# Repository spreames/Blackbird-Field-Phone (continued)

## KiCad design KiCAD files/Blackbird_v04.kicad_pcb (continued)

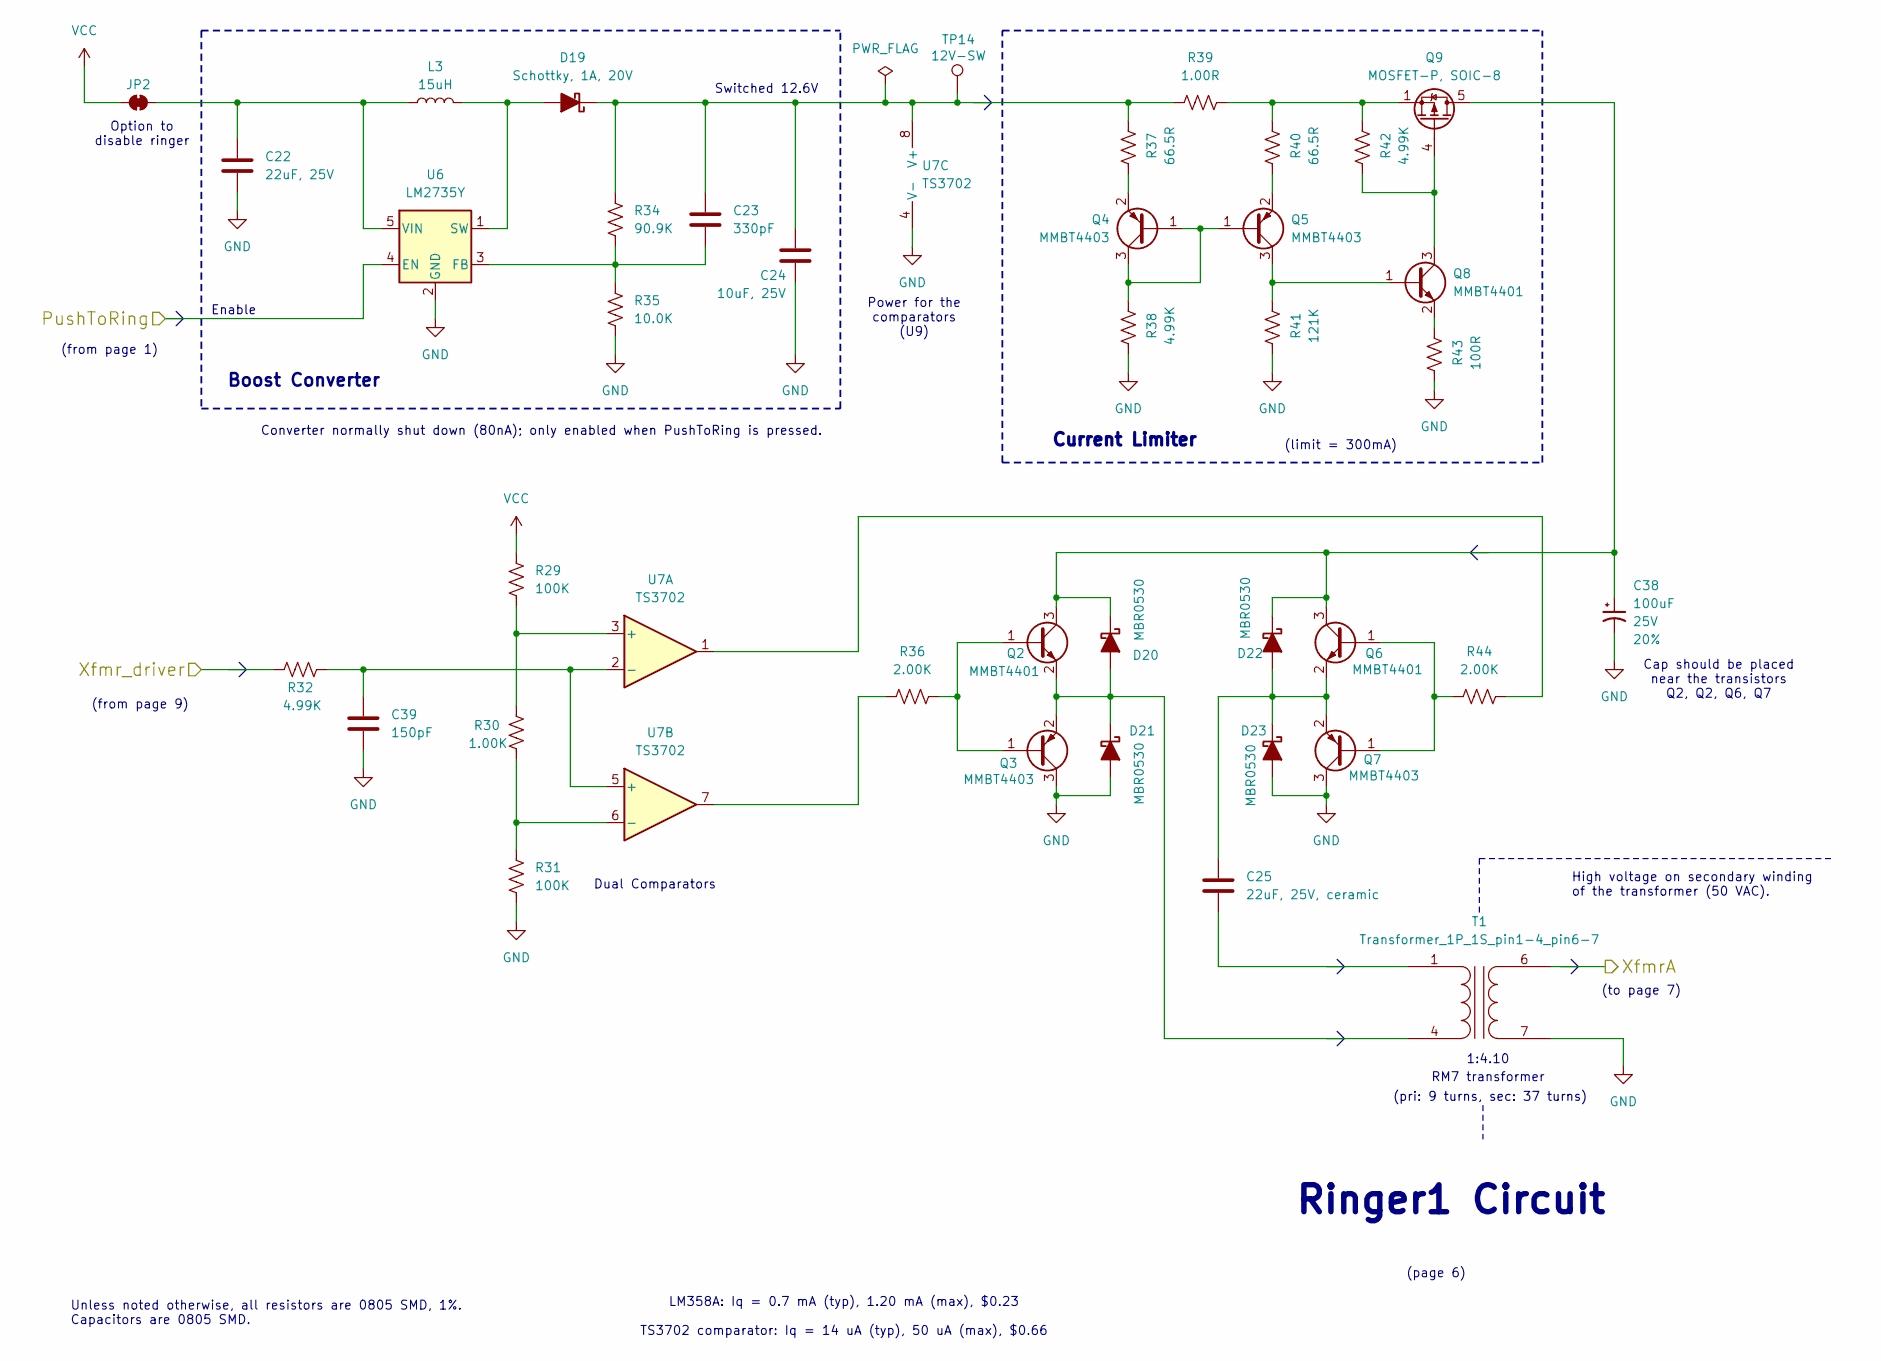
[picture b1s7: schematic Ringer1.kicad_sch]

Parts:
C22: 22uF, 25V; C_0805_2012Metric_Pad1.18x1.45mm_HandSolder
C23: 330pF; C_0805_2012Metric_Pad1.18x1.45mm_HandSolder
C24: 10uF, 25V; C_0805_2012Metric_Pad1.18x1.45mm_HandSolder
C25: 22uF, 25V, ceramic; C_0805_2012Metric_Pad1.18x1.45mm_HandSolder
C38: 100uF; Panasonic_D; Voltage 25V; Tolerance 20%
C39: 150pF; C_0805_2012Metric_Pad1.18x1.45mm_HandSolder
D19: Schottky, 1A, 20V; D_SOD-123
D20, D21, D22, D23: MBR0530; D_SOD-123
JP2: Jumper_2_NC_Trace
L3: 15uH; L_5x5mm_or_6.3x6.0
Q2, Q6, Q8: MMBT4401; SOT-23_Handsoldering
Q3, Q4, Q5, Q7: MMBT4403; SOT-23_Handsoldering
Q9: MOSFET-P, SOIC-8; SOIC-8_3.9x4.9mm_P1.27mm
R29, R31: 100K; R_0805_2012Metric_Pad1.20x1.40mm_HandSolder
R30: 1.00K; R_0805_2012Metric_Pad1.20x1.40mm_HandSolder
R32, R38, R42: 4.99K; R_0805_2012Metric_Pad1.20x1.40mm_HandSolder
R34: 90.9K; R_0805_2012Metric_Pad1.20x1.40mm_HandSolder
R35: 10.0K; R_0805_2012Metric_Pad1.20x1.40mm_HandSolder
R36, R44: 2.00K; R_0805_2012Metric_Pad1.20x1.40mm_HandSolder
R37, R40: 66.5R; R_0805_2012Metric_Pad1.20x1.40mm_HandSolder
R39: 1.00R; R_0805_2012Metric_Pad1.20x1.40mm_HandSolder
R41: 121K; R_0805_2012Metric_Pad1.20x1.40mm_HandSolder
R43: 100R; R_0805_2012Metric_Pad1.20x1.40mm_HandSolder
T1: Transformer_1P_1S_pin1-4_pin6-7; Transformer_RM7_8-pin
TP14: 12V-SW; Test_point_47mil_scope_probe
U6: LM2735Y; SOT-23-5
U7: TS3702; SOIC-8_3.9x4.9mm_P1.27mm

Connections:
/Clocks/Xfmr_driver: R32.2; also elsewhere on the board
/Ringer1/XfmrA: T1.6 (SB); also elsewhere on the board
GND: C22.2, C24.2, C38.2, C39.2, D21.2 (A), D23.2 (A), Q3.3 (C), Q7.3 (C), R31.1, R35.1, R38.2, R41.2, R43.2, T1.7 (SA), U6.2 (GND), U7.4 (V-); also elsewhere on the board
unnamed: D19.2 (A), L3.2, U6.1 (SW)
unnamed: C23.1, C24.1, D19.1 (K), R34.2, R37.1, R39.2, TP14.1, U7.8 (V+)
unnamed: D20.2 (A), D21.1 (K), Q2.2 (E), Q3.2 (E), T1.4 (AB)
unnamed: C38.1, D20.1 (K), D22.1 (K), Q2.3 (C), Q6.3 (C), Q9.5 (D), Q9.6 (D), Q9.7 (D), Q9.8 (D)
unnamed: C25.1, D22.2 (A), D23.1 (K), Q6.2 (E), Q7.2 (E)
unnamed: C22.1, JP2.2 (B), L3.1, U6.5 (VIN)
unnamed: Q2.1 (B), Q3.1 (B), R36.1
unnamed: Q4.1 (B), Q4.3 (C), Q5.1 (B), R38.1
unnamed: Q4.2 (E), R37.2
unnamed: Q5.3 (C), Q8.1 (B), R41.1
unnamed: Q5.2 (E), R40.2
unnamed: Q6.1 (B), Q7.1 (B), R44.2
unnamed: Q8.3 (C), Q9.4 (G), R42.2
unnamed: Q8.2 (E), R43.1
unnamed: Q9.1 (S), Q9.2 (S), Q9.3 (S), R39.1, R40.1, R42.1
unnamed: R36.2, U7.7
unnamed: R44.1, U7.1
unnamed: C25.2, T1.1 (AA)
unnamed: C23.2, R34.1, R35.2, U6.3 (FB)
unnamed: R29.1, R30.2, U7.3 (+)
unnamed: C39.1, R32.1, U7.2 (-), U7.5 (+)
unnamed: R30.1, R31.2, U7.6 (-)
PushToRing: U6.4 (EN); also elsewhere on the board
VCC: JP2.1 (A), R29.2; also elsewhere on the board

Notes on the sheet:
Dual Comparators
Enable
(from page 9)
Ringer1 Circuit
RM7 transformer
Converter normally shut down (80nA); only enabled when PushToRing is pressed.
1:4.10
Boost Converter
(pri: 9 turns, sec: 37 turns)
High voltage on secondary winding of the transformer (50 VAC).
Option to disable ringer
Power for the comparators (U9)
Current Limiter
(to page 7)
Unless noted otherwise, all resistors are 0805 SMD, 1%. Capacitors are 0805 SMD.
LM358A: Iq = 0.7 mA (typ), 1.20 mA (max), $0.23 TS3702 comparator: Iq = 14 uA (typ), 50 uA (max), $0.66
(limit = 300mA)
Cap should be placed near the transistors Q2, Q2, Q6, Q7
(page 6)
(from page 1)
Switched 12.6V

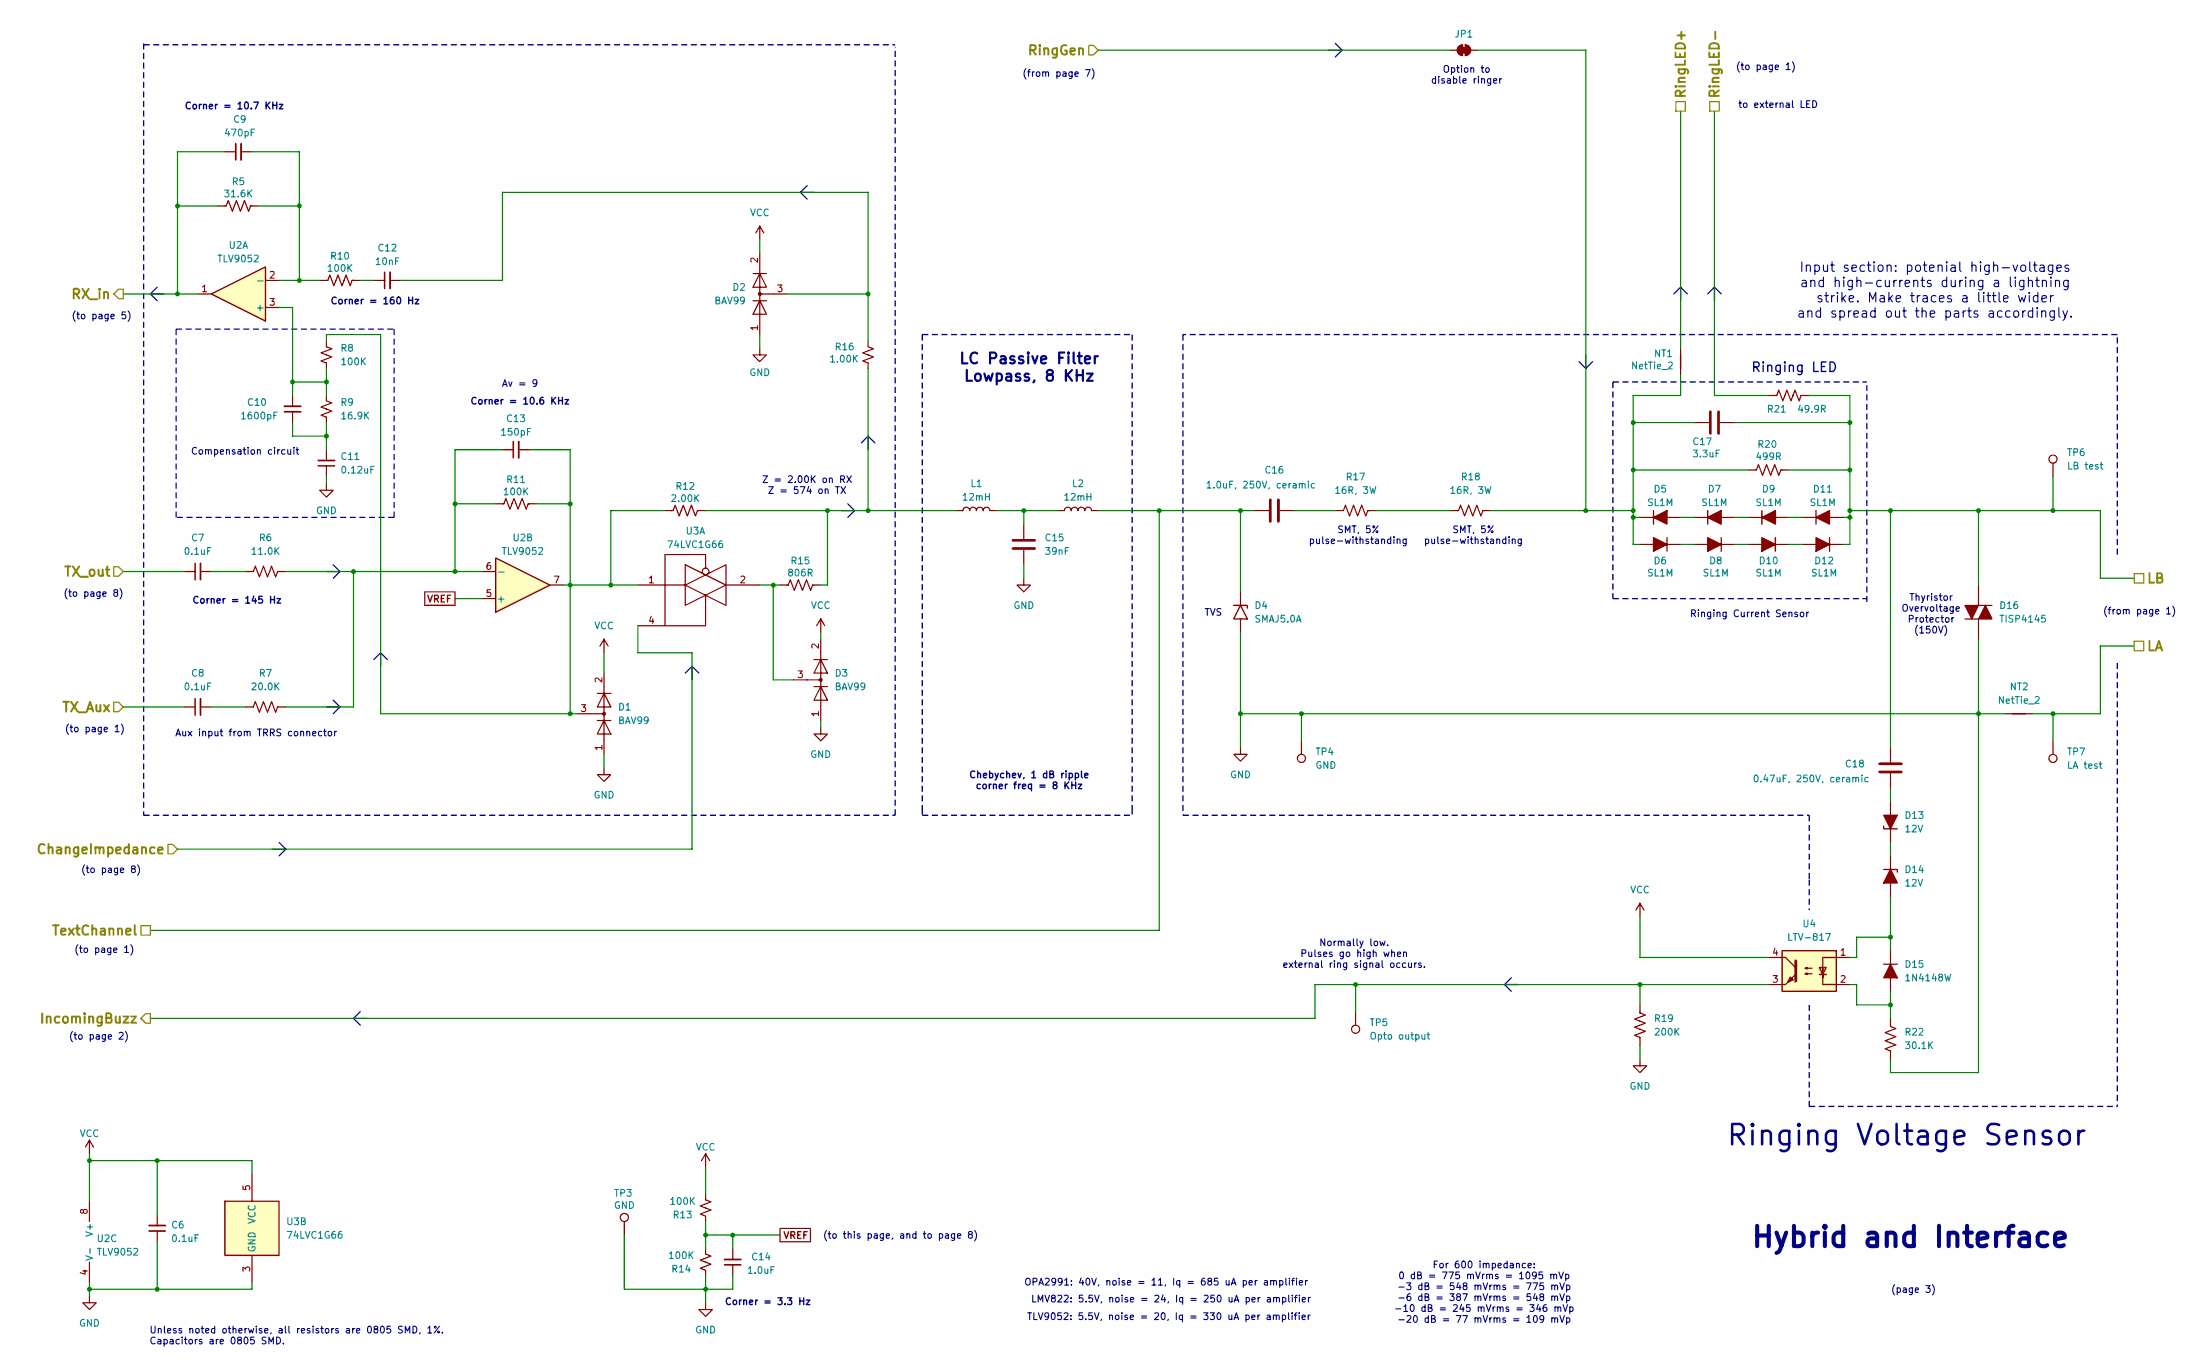
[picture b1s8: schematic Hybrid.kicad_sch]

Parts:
C6, C7, C8: 0.1uF; C_0805_2012Metric_Pad1.18x1.45mm_HandSolder
C9: 470pF; C_0805_2012Metric_Pad1.18x1.45mm_HandSolder
C10: 1600pF; C_0805_2012Metric_Pad1.18x1.45mm_HandSolder
C11: 0.12uF; C_0805_2012Metric_Pad1.18x1.45mm_HandSolder
C12: 10nF; C_0805_2012Metric_Pad1.18x1.45mm_HandSolder
C13: 150pF; C_0805_2012Metric_Pad1.18x1.45mm_HandSolder
C14: 1.0uF; C_0805_2012Metric_Pad1.18x1.45mm_HandSolder
C15: 39nF; C_0805_2012Metric_Pad1.18x1.45mm_HandSolder
C16: 1.0uF, 250V, ceramic; C_1825_4564Metric_Pad1.57x6.80mm_HandSolder
C17: 3.3uF; C_0805_2012Metric_Pad1.18x1.45mm_HandSolder
C18: 0.47uF, 250V, ceramic; C_1812_4532Metric_Pad1.57x3.40mm_HandSolder
D1, D2, D3: BAV99; SOT-23
D4: SMAJ5.0A; D_SMA
D5, D6, D7, D8, D9, D10, D11, D12: SL1M; D_SOD-123F
D13, D14: 12V; D_SOD-123
D15: 1N4148W; D_SOD-123
D16: TISP4145; D_SMB_Handsoldering
JP1: Jumper_2_NC_Trace
L1, L2: 12mH; L_Radial_D8.7mm_P5.00mm_Fastron_07HCP
NT1, NT2: NetTie_2; NetTie-2_SMD_Pad0.5mm
R5: 31.6K; R_0805_2012Metric_Pad1.20x1.40mm_HandSolder
R6: 11.0K; R_0805_2012Metric_Pad1.20x1.40mm_HandSolder
R7: 20.0K; R_0805_2012Metric_Pad1.20x1.40mm_HandSolder
R8, R10, R11, R13, R14: 100K; R_0805_2012Metric_Pad1.20x1.40mm_HandSolder
R9: 16.9K; R_0805_2012Metric_Pad1.20x1.40mm_HandSolder
R12: 2.00K; R_0805_2012Metric_Pad1.20x1.40mm_HandSolder
R15: 806R; R_0805_2012Metric_Pad1.20x1.40mm_HandSolder
R16: 1.00K; R_0805_2012Metric_Pad1.20x1.40mm_HandSolder
R17, R18: 16R, 3W; R_2512_6332Metric_wide
R19: 200K; R_0805_2012Metric_Pad1.20x1.40mm_HandSolder
R20: 499R; R_0805_2012Metric_Pad1.20x1.40mm_HandSolder
R21: 49.9R; R_0805_2012Metric_Pad1.20x1.40mm_HandSolder
R22: 30.1K; R_0805_2012Metric_Pad1.20x1.40mm_HandSolder
TP3, TP4: GND; Test_point_47mil_scope_probe
TP5: Opto output; Test_point_47mil_scope_probe
TP6: LB test; Test_point_47mil_scope_probe
TP7: LA test; Test_point_47mil_scope_probe
U2: TLV9052; SOIC-8_3.9x4.9mm_P1.27mm
U3: 74LVC1G66; SOT-23-5_HandSoldering
U4: LTV-817; Opto_LTV-817S

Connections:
/Clocks/IncomingBuzz: R19.1, TP5.1, U4.3; also elsewhere on the board
/Equalizer/RX_in: C9.1, R5.1, U2.1; also elsewhere on the board
/Hybrid/ChangeImpedance: U3.4; also elsewhere on the board
/Hybrid/LA: NT2.2, TP7.1; also elsewhere on the board
/Hybrid/LB: C17.2, C18.1, D11.2 (A), D12.1 (K), D16.1, R20.2, R21.2, TP6.1; also elsewhere on the board
/Hybrid/RingGen: JP1.1 (A); also elsewhere on the board
/Hybrid/RingLED+: NT1.2; also elsewhere on the board
/Hybrid/RingLED-: R21.1; also elsewhere on the board
/Hybrid/TX_Aux: C8.1; also elsewhere on the board
/Hybrid/TX_out: C7.1; also elsewhere on the board
/Hybrid/TextChannel: C16.1, D4.1 (A1), L2.2; also elsewhere on the board
GND: C6.1, C11.1, C14.1, C15.2, D1.1 (K), D2.1 (K), D3.1 (K), D4.2 (A2), D16.2, NT2.1, R14.1, R19.2, R22.2, TP3.1, TP4.1, U2.4 (V-), U3.3 (GND); also elsewhere on the board
unnamed: C7.2, R6.1
unnamed: C8.2, R7.1
unnamed: C10.1, C11.2, R9.1
unnamed: C12.1, R10.2
unnamed: C12.2, D2.3 (K), R16.2
unnamed: C13.2, D1.3 (K), R8.2, R11.2, R12.1, U2.7, U3.1
unnamed: C15.1, L1.2, L2.1
unnamed: C16.2, R17.1
unnamed: D3.3 (K), R15.1, U3.2
unnamed: D5.2 (A), D7.1 (K)
unnamed: C17.1, D5.1 (K), D6.2 (A), JP1.2 (B), NT1.1, R18.2, R20.1
unnamed: D6.1 (K), D8.2 (A)
unnamed: D7.2 (A), D9.1 (K)
unnamed: D8.1 (K), D10.2 (A)
unnamed: D10.1 (K), D12.2 (A)
unnamed: D9.2 (A), D11.1 (K)
unnamed: C18.2, D13.2 (A)
unnamed: D13.1 (K), D14.1 (K)
unnamed: D14.2 (A), D15.1 (K), U4.1
unnamed: D15.2 (A), R22.1, U4.2
unnamed: L1.1, R12.2, R15.2, R16.1
unnamed: R17.2, R18.1
unnamed: C10.2, R8.1, R9.2, U2.3 (+)
unnamed: C9.2, R5.2, R10.1, U2.2 (-)
unnamed: C13.1, R6.2, R7.2, R11.1, U2.6 (-)
VCC: C6.2, D1.2 (A), D2.2 (A), D3.2 (A), R13.2, U2.8 (V+), U3.5 (VCC), U4.4; also elsewhere on the board
VREF: C14.2, R13.1, R14.2, U2.5 (+); also elsewhere on the board

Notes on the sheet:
(to page 1)
For 600 impedance: 0 dB = 775 mVrms = 1095 mVp -3 dB = 548 mVrms = 775 mVp -6 dB = 387 mVrms = 548 mVp -10 dB = 245 mVrms = 346 mVp -20 dB = 77 mVrms = 109 mVp
SMT, 5% pulse-withstanding
(to this page, and to page 8)
TLV9052: 5.5V, noise = 20, Iq = 330 uA per amplifier
(to page 8)
Option to disable ringer
Z = 2.00K on RX Z = 574 on TX
Compensation circuit
Input section: potenial high-voltages and high-currents during a lightning strike. Make traces a little wider and spread out the parts accordingly.
(to page 2)
LMV822: 5.5V, noise = 24, Iq = 250 uA per amplifier
(page 3)
(from page 1)
Unless noted otherwise, all resistors are 0805 SMD, 1%. Capacitors are 0805 SMD.
(from page 7)
Chebychev, 1 dB ripple corner freq = 8 KHz
Aux input from TRRS connector
Ringing Voltage Sensor
(to page 5)
Thyristor Overvoltage Protector (150V)
Corner = 10.7 KHz
to external LED
Corner = 160 Hz
TVS
Av = 9
LC Passive Filter Lowpass, 8 KHz
Corner = 145 Hz
Hybrid and Interface
Normally low. Pulses go high when external ring signal occurs.
OPA2991: 40V, noise = 11, Iq = 685 uA per amplifier
Ringing Current Sensor
Corner = 10.6 KHz
Corner = 3.3 Hz
Ringing LED

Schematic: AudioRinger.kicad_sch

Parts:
C1, C2, C5: 0.1uF; C_0805_2012Metric_Pad1.18x1.45mm_HandSolder
C3: 2.2uF; C_0805_2012Metric_Pad1.18x1.45mm_HandSolder
C4: 22uF; C_0805_2012Metric_Pad1.18x1.45mm_HandSolder
R2, R4: 20.0K; R_0805_2012Metric_Pad1.20x1.40mm_HandSolder
R3: 10.0K; R_0805_2012Metric_Pad1.20x1.40mm_HandSolder
U1: TPA321; SOIC-8_3.9x4.9mm_P1.27mm

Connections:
/AudioBuzzer/Buzz-A: R4.1, U1.5 (Vo+); also elsewhere on the board
/AudioBuzzer/Buzz-B: U1.8 (Vo-); also elsewhere on the board
/AudioBuzzer/Buzzer_Amp_Enable: U1.1 (SHDN); also elsewhere on the board
/AudioBuzzer/Buzzer_Amp_Signal: C2.1; also elsewhere on the board
/AudioBuzzer/ToneInjection: C1.1; also elsewhere on the board
GND: C3.2, C4.2, C5.2, U1.7 (GND); also elsewhere on the board
unnamed: C1.2, R2.2
unnamed: C2.2, R3.2
unnamed: C3.1, U1.2 (BYP), U1.3 (IN+)
unnamed: R2.1, R3.1, R4.2, U1.4 (IN-)
VCC: C4.1, C5.1, U1.6 (VDD); also elsewhere on the board

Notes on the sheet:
Shutdown is enabled most of the time. When a pulse comes by, then the tone is enabled for a short time.
Audio Ringer
(to page 1)
(page 2)
Unless noted otherwise, all resistors are 0805 SMD, 1%. Capacitors are 0805 SMD.
Audio Amplifier
(from page 1)
(from page 9)
To Buzzer
This port gives us the option to add a sound at the buzzer speaker from text messages or some other auxiliary function.

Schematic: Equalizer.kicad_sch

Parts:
C33: 39nF; C_0805_2012Metric_Pad1.18x1.45mm_HandSolder
C34: 560pF; C_0805_2012Metric_Pad1.18x1.45mm_HandSolder
C35: 0.1uF; C_0805_2012Metric_Pad1.18x1.45mm_HandSolder
C36: 390nF; C_0805_2012Metric_Pad1.18x1.45mm_HandSolder
C37: 5.6nF; C_0805_2012Metric_Pad1.18x1.45mm_HandSolder
R63, R69: 332R; R_0805_2012Metric_Pad1.20x1.40mm_HandSolder
R64, R70: 845R; R_0805_2012Metric_Pad1.20x1.40mm_HandSolder
R65, R71: 143K; R_0805_2012Metric_Pad1.20x1.40mm_HandSolder
R66, R72: 9.09K; R_0805_2012Metric_Pad1.20x1.40mm_HandSolder
R67, R73: 464R; R_0805_2012Metric_Pad1.20x1.40mm_HandSolder
R68, R74: 5.60K; R_0805_2012Metric_Pad1.20x1.40mm_HandSolder
U13: TLV9001; SOT-23-5_HandSoldering
U14: TLV9002; SOIC-8_3.9x4.9mm_P1.27mm

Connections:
/Equalizer/EqualOut: R68.2, U14.1; also elsewhere on the board
/Equalizer/RX_in: R74.1; also elsewhere on the board
GND: C35.1, U13.2 (V-), U14.4 (V-); also elsewhere on the board
unnamed: C33.1, R64.1
unnamed: C33.2, R63.1, R66.2
unnamed: C34.2, R64.2, R67.1
unnamed: C36.1, R70.1
unnamed: C36.2, R69.1, R72.2
unnamed: C37.2, R70.2, R73.1
unnamed: C34.1, R65.1, U13.3 (+)
unnamed: R67.2, U13.1, U13.4 (-)
unnamed: R66.1, R72.1, R74.2, U14.3 (+)
unnamed: R63.2, R68.1, R69.2, U14.2 (-)
unnamed: C37.1, R71.1, U14.5 (+)
unnamed: R73.2, U14.6 (-), U14.7
VCC: C35.2, U13.5 (V+), U14.8 (V+); also elsewhere on the board
VREF: R65.2, R71.2; also elsewhere on the board

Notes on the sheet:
RX Equalizer
Need to adjust values for 5 KHz
(to page 5)
Resonance
(page 11)
Center Freq
5 KHz Equalizer
(half Vcc)
400 Hz Equalizer
(from page 3)
TLV9001: 5.5V, noise = 27, Iq = 77 uA (max) TLV9002: 5.5V, noise = 27, Iq = 75 uA (max) per amplifier
This page is an graphic equalizer, except it only controls two bands and the gain and Q are fixed. For more info: An audio circuit collection, Part 3 Texas Instruments https://www.ti.com/lit/pdf/slyt134 Simple, Easy Parametric and Graphic EQ's, Plus Peaks and Notches http://www.geofex.com/article_f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
Unless noted otherwise, all resistors are 0805 SMD, 1%. Capacitors are 0805 SMD.
Sets Q

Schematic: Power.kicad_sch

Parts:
NT3: NetTie_2; NetTie-2_SMD_Pad0.5mm
Q1: NMOS; SOT-23_Handsoldering
R23: 499K; R_0805_2012Metric_Pad1.20x1.40mm_HandSolder

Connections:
/Power/Battery+: NT3.1; also elsewhere on the board
/Power/Battery-: Q1.3 (D); also elsewhere on the board
GND: Q1.2 (S), R23.1; also elsewhere on the board
VCC: NT3.2, Q1.1 (G), R23.2; also elsewhere on the board

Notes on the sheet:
Power can come from three AA batteries or one Li-on 18650 cell. * Three alkaline AA batteries have a nominal voltage of 4.5V (max 4.8V). * Three lithium AA batteries (primary, not rechargeable) have a new voltage of 5.4V * 18650 cell has nominal voltage of 4.2 fully charged, 3.7V nominal. * All cel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
(to all pages)
(from page 1)
(page 4)
Reverse-battery protection
Unless noted otherwise, all resistors are 0805 SMD, 1%. Capacitors are 0805 SMD.
Voltage = (3.0V, 4.5V, 5.5V)
Power

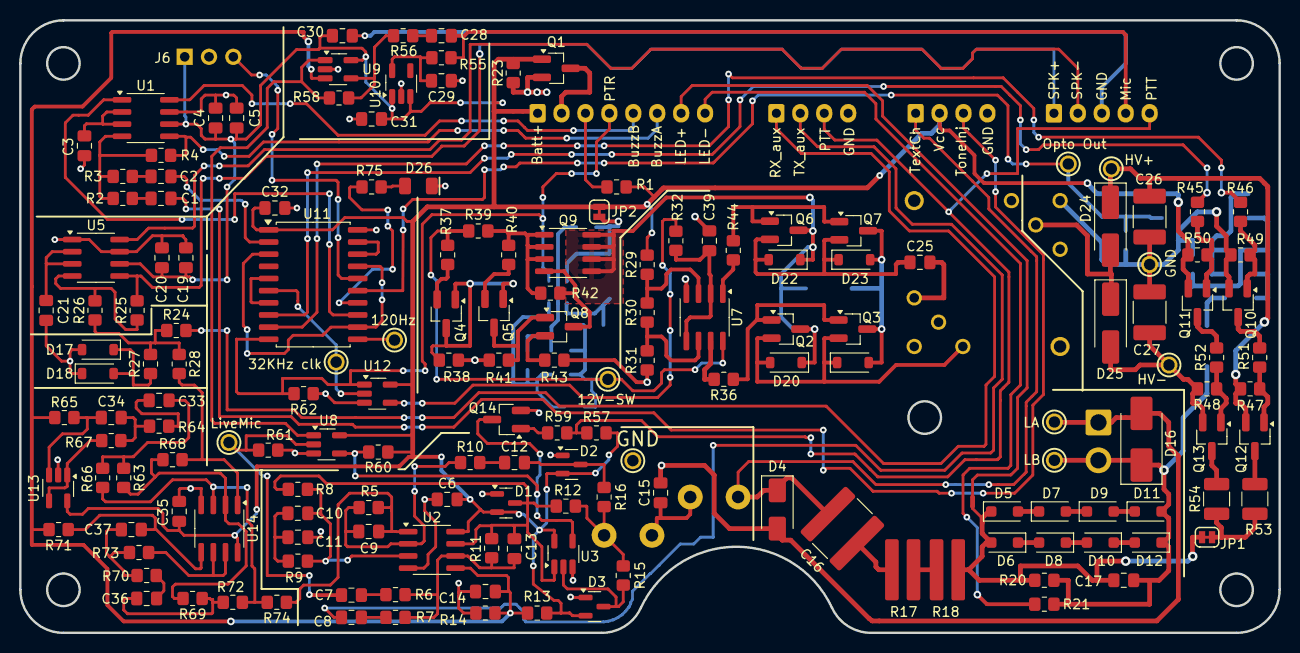
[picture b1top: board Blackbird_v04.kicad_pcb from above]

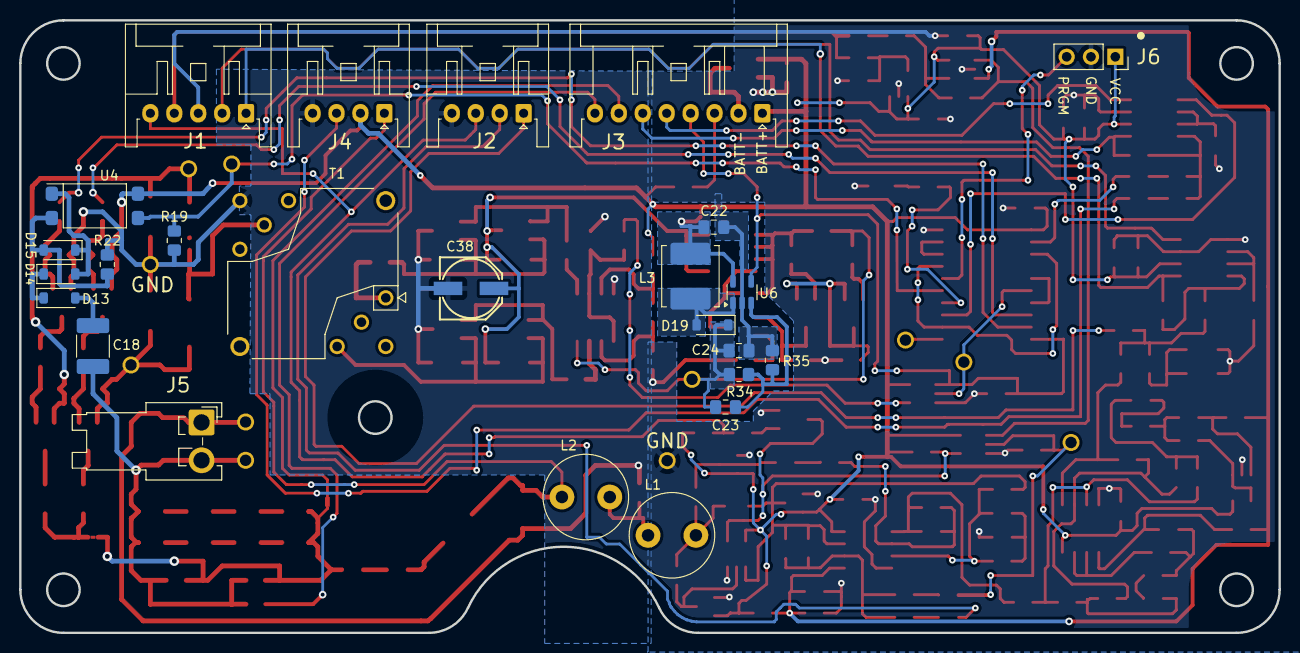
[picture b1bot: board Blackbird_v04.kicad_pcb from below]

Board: 2 copper layers, 131.6 x 64.0 mm, 193 parts (25 on the bottom side), 122 nets.

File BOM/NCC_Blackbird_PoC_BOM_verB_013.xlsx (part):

MME P/N | REV | DWG No | PART DESCRIPTION | REF. DES. | QTY | UOM | Make/Buy | MFGR-1 | MFGR-1 P/N | DIST-1 | DIST-1 P/N | MFGR-2 | MFGR-2 P/N | MFGR-3 | MFGR-3 P/N | Cost (1) | Ext. Cost (1) | Cost (10) | Ext Cost (10)
 |  |  | Top Level – Blackbird Proof-of-Concept Field Phone
 |  |  | Main PCB Assy |  | 1 | EA | M
 |  |  | Handset Assy |  | 1 | EA | M
 |  |  | Base Unit Assy |  | 1 | EA | M
 |  |  | Battery, 18650 |  | 1 | EA | B
 |  |  | Battery, AA |  | 3 | EA | B
MME P/N | REV | DWG No | PART DESCRIPTION | REF. DES. | QTY | UOM | Make/Buy | MFGR-1 | MFGR-1 P/N | DIST-1 | DIST-1 P/N | MFGR-2 | MFGR-2 P/N | MFGR-3 | MFGR-3 P/N | Cost (1) | Ext. Cost (1) | Cost (10) | Ext Cost (10)
 |  |  | Handset Assy
 |  |  | Speaker, IP67, 30mm, WSPH-3005 |  | 1 | EA | B | Soberton Inc. | WSPH-3005 | Digikey | 433-1284-ND |  |  |  |  | 3.03 | 3.03 | 2.2792 | 2.2792
 |  |  | Microphone, 6mm dia, electret |  | 1 | EA | B | Soberton Inc. | EM6027LW-42C | Digikey | 433-1154-ND |  |  |  |  | 1.68 | 1.68 | 1.371 | 1.371
 |  |  | Switch, momentary pushbutton, for PTT | M1 | 1 | EA | B | Judco Manufacturing Inc. | 40-2390-00 | Digikey | 506PB-ND |  |  |  |  | 2.35 | 2.35 | 2.034 | 2.034 | old switch
 |  | xxx | Microphone Insert, 82A filament, Recreus FilaFlex |  | 1 | EA | M |  |  |  |  |  |  |  |  | 0.15 | 0.15 | 0.15 | 0.15
 |  |  | Cable, 5 cond, 5 x 0.34mm (22 AWG) |  | 1.5 | m | B | Helukabel | 49608 | TME | STR-PUR5X0.34 |  |  |  |  | 4.87 | 7.305 | 2.416 | 3.624
 |  |  | Cable gland, with pigtail |  | 1 | EA | B | Heyco Products Corp | 3237 | Digikey | 3720-3237-ND |  |  |  |  | 1.78 | 1.78 | 1.513 | 1.513
 |  |  | Screw, 316 SS, Button Head, Hex Drive, M3 x 0.5mm, 10mm Long |  | 13 | EA | B | McMaster | 94500A223 |  |  |  |  |  |  | 0.0874 | 1.1362 | 0.0874 | 1.1362 | uses 2.5mm hex driver
 |  |  | Connector,butt splice, 22-26 AWG, crimp |  | 5 | EA | B | TE Conn AMP Connectors | 321026 | Digikey | A27461 |  |  |  |  | 0.39 | 1.95 | 0.3132 | 1.566
 |  |  | Connector, butt splice,
 |  |  | Brass Heat-Set Inserts for Plastic, M3 x 5.7mm | M3 | 13 | EA | B | CNC Kitchen | M3x5.7 | CNC Kitchen |  | McMaster | 97171A310 |  |  | 0.21 | 2.73 | 0.121 | 1.573
 |  | xxx | Filament, 3D printer, PCTG, Handset Cover, 2 copies |  | 26 | gm | M | 3D Fuel | Pro PCTG filament |  |  |  |  |  |  | 0.0399 | 1.0374 | 0.0399 | 1.0374 | based on PCTG
 |  | xxx | Filament, 3D printer, PCTG, Handset, Left body |  | 57 | gm | M | 3D Fuel | Pro PCTG filament |  |  |  |  |  |  | 0.0399 | 2.2743 | 0.0399 | 2.2743 | based on PCTG
 |  | xxx | Filament, 3D printer, PCTG, Handset, Right body |  | 58 | gm | M | 3D Fuel | Pro PCTG filament |  |  |  |  |  |  | 0.0399 | 2.3142 | 0.0399 | 2.3142 | based on PCTG
MME P/N | REV | DWG No | PART DESCRIPTION | REF. DES. | QTY | UOM | Make/Buy | MFGR-1 | MFGR-1 P/N | DIST-1 | DIST-1 P/N | MFGR-2 | MFGR-2 P/N | MFGR-3 | MFGR-3 P/N | Cost (1) | Ext. Cost (1) | Cost (10) | Ext Cost (10)
 |  |  | Base Unit Assy
 |  |  | Diode, LED, red, T ¾ package (5mm), 60 deg, 700 mcd | D200 | 1 | EA | B | Lumex Opto/Components Inc. | SSL-LX5093SID | Digikey | 67-2288-ND | Kingbright | WP63SURDK |  |  | 0.68 | 0.68 | 0.402 | 0.402
 |  |  | Diode mounting, for 1 ¾ package | LED mounting | 1 | EA | B | Lumex Opto/Components Inc. | SSH-LX5091 | Digikey | 67-1332-ND |  |  |  |  | 0.33 | 0.33 | 0.177 | 0.177
 |  |  | LED mounting,
 |  |  | Speaker, 8 ohm, square, for buzzer |  | 1 | EA | B | Wolff Electronics | OWS-131845W50A-8 | Digikey | 3949-OWS-131845W50A-8-ND |  |  |  |  | 1.51 | 1.51 | 1.184 | 1.184
 |  |  | Terminal Post, for comm line connection |  | 2 | EA | B | CLIFF Electronics | CL681561 | Digikey | 4654-CL681561-ND |  |  |  |  | 2.23 | 4.46 | 2.091 | 4.182
 |  |  | Connector, TRRS, 3.5mm, panel mount (aux connector) |  | 1 | EA | B | Same Sky (Formerly CUI Devices) | SJ5-43502PM | Digikey | CP5-43502PM-ND |  |  |  |  | 2.43 | 2.43 | 2.068 | 2.068
 |  |  | Cable gland with pigtail, PG7, nylon, range 2.9-6.35mm |  | 1 | EA | B | Heyco | 3237 | Digikey | 3720-3237-ND |  |  |  |  | 1.78 | 1.78 | 1.513 | 1.513
 |  |  | Switch, momentary pushbutton, for Ringer, waterproof | M2 | 1 | EA | B | CIT Relay and Switch | FHNDSBX | Digikey | 2449-FHNDSBX-ND | E-Switch | PV0H240SS |  |  | 7.77 | 7.77 | 7.77 | 7.77 | new switch
 |  |  | Brass Heat-Set Inserts for Plastic, M3 x 5.7mm | M3 | 7 | EA | B | CNC Kitchen | M3x5.7 | CNC Kitchen |  | McMaster | 97171A310 |  |  | 0.21 | 1.47 | 0.121 | 0.847
 |  |  | Brass Heat-Set Inserts for Plastic, ¼-20 | M4 | 1 | EA | B | McMaster | 93365A160 |  |  |  |  |  |  | 0.209 | 0.209 | 0.209 | 0.209
 |  |  | Screw, 316 SS, Button Head, Hex Drive, M3 x 0.5mm, 10mm Long | uses 2.5mm hex driver | 7 | EA | B | McMaster | 94500A223 |  |  |  |  |  |  | 0.0874 | 0.6118 | 0.0874 | 0.6118
 |  |  | Rod, 304 SS Rod, 3 mm Diameter |  | 0.2 | FT | B | McMaster | 1272T33 |  |  |  |  |  |  | 3.77 | 0.754 | 3.77 | 0.754
 |  |  | Battery Contact, leaf, 1017-1 | battery door side | 3 | EA | B | Keystone Electronics | 1017-1 | Digikey | 36-1017-1-ND |  |  |  |  | 0.19 | 0.57 | 0.154 | 0.462
 |  |  | Battery Contact, leaf, 209 | inside of the case | 3 | EA | B | Keystone Electronics | 209 | Digikey | 36-209-ND |  |  |  |  | 0.25 | 0.75 | 0.205 | 0.615
 |  |  | O-ring, large, for case |  | 1 | EA | B | McMaster-Carr | 1302N156 |  |  |  |  |  |  | 8.24 | 8.24 | 1.64 | 1.64 | bag of 5
 |  |  | O-ring, medium, for battery door |  | 1 | EA | B | McMaster-Carr | 9262K529 |  |  |  |  |  |  | 7.17 | 7.17 | 0.2868 | 0.2868 | bag of 25
 |  |  | Cable gland, with pigtail |  | 1 | EA | B | Heyco Products Corp | 3237 | Digikey | 3720-3237-ND |  |  |  |  | 1.78 | 1.78 | 1.513 | 1.513
 |  |  | Ring lug, 4mm or #8, non-insulated | for comm line conn. | 2 | EA | B | Amazon |  |  |  |  |  |  |  | 13.94 | 27.88 | 0.087125 | 0.17425 | https://www.amazon.com/dp/B0CYBZDDG6
 |  |  | D-ring, 1/4-20 tripod mounting, stainless | for battery door | 1 | EA | B | Amazon |  |  |  |  |  |  |  | 1.6 | 1.6 | 1.6 | 1.6 | https://www.amazon.com/dp/B0CR1PKCG3
 |  |  | rubber seal for D-ring | for battery door | 1 | EA | B
 |  | xxx | Filament, 3D printer, PCTG, CASE |  | 226 | gm | M | 3D Fuel | Pro PCTG filament |  |  |  |  |  |  | 0.0399 | 9.0174 | 0.0399 | 9.0174 | based on PCTG
 |  | xxx | Filament, 3D printer, PCTG, Case Cover |  | 22 | gm | M | 3D Fuel | Pro PCTG filament |  |  |  |  |  |  | 0.0399 | 0.8778 | 0.0399 | 0.8778 | based on PCTG
 |  | xxx | Filament, 3D printer, PCTG, Battery Cover |  | 24 | gm | M | 3D Fuel | Pro PCTG filament |  |  |  |  |  |  | 0.0399 | 0.9576 | 0.0399 | 0.9576 | based on PCTG
MME P/N | REV | DWG No | PART DESCRIPTION | REF. DES. | QTY | UOM | Make/Buy | MFGR-1 | MFGR-1 P/N | DIST-1 | DIST-1 P/N | MFGR-2 | MFGR-2 P/N | MFGR-3 | MFGR-3 P/N | Cost (1) | Ext. Cost (1) | Cost (10) | Ext Cost (10)
 |  |  | Internal Cables
 |  |  | Connector, JST XA, 8-pin, right angle, receptacle, TH | J1A | 1 | EA | B | JST Sales America Inc. | XAP-08V-1 | Digikey | 455-2154-ND |  |  |  |  | 0.19 | 0.19 | 0.162 | 0.162
 |  |  | Connector, JST XA, 4-pin, right angle, receptacle, TH | J2A, J6A | 2 | EA | B | JST Sales America Inc. | XAP-04V-1 | Digikey | 455-2150-ND |  |  |  |  | 0.1 | 0.2 | 0.077 | 0.154
 |  |  | Connector, JST VH, 2-pin, right angle, receptacle, TH | J3A | 1 | EA | B | JST Sales America Inc. | VHR-2N | Digikey | 455-VHR-2N-ND | JST Sales America Inc. | VHR-2M |  |  | 0.1 | 0.1 | 0.066 | 0.066
 |  |  | Connector, JST XA, 5-pin, right angle, receptacle,TH | J4A | 1 | EA | B | JST Sales America Inc. | XAP-05V-1 | Digikey | 455-2151-ND |  |  |  |  | 0.1 | 0.1 | 0.083 | 0.083
 |  |  | Connector, pins for JST XA connectors | pins for XA conn. | 21 | EA | B | JST Sales America Inc. | SXA-001T-P0.6 | Digikey | 455-1904-500-ND |  |  |  |  | 0.0246 | 0.5166 | 0.0246 | 0.5166 | strips of 100, 500, or 1000
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
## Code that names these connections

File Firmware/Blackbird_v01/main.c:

/*
 * main.c
 *
 * Created: 29-Sep-2025
 * Updated: 9-Nov-2025
 * Author : Steve Reames
 * Released to Creative Commons
 */ 

/* Pinout
	PA0 = UDPI programming pin (in/out)
	PA1 = <unused>
	PA2 = <unused>
	PA3 = <unused>
	PA4 = <unused>
	PA5 = TCB0, WO, Buzz_clk (output)
	PA6 = <unused>
	PA7 = <unused>
	
	PB0 = TCA0, WO0, 20Hz_clk (output)
	PB1 = PushToRing (input)
	PB2 = EnHVpositive (output)
	PB3 - EnHVnegative (output)
	PB4 = 20Hz_clk (input)
	PB5 = CLKOUT (output)
	
	PC0 = Buzz_clk (input)
	PC1 = EnBuzzerAmp (output)
	PC2 = BuzzerAmpInput (output)
	PC3 = IncomingBuzz (input)
*/

#include "Blackbird.h"


/*****************************************************************************/
/*                            Hardware Fuses                                 */
/*****************************************************************************/
//
FUSES = {
	.WDTCFG = PERIOD_OFF_gc || WINDOW_OFF_gc,  /* Watchdog Configuration - off */
	.BODCFG = ACTIVE_DIS_gc,  /* BOD Configuration - BOD disabled */
	.OSCCFG = FREQSEL_16MHZ_gc,  /* Oscillator Configuration */
	//	.reserved_1[2];
	.SYSCFG0 = CRCSRC_NOCRC_gc || RSTPINCFG_UPDI_gc,	/* System Configuration 0 - CRC & UPDI programming pin */
	.SYSCFG1 = SUT_8MS_gc,  /* System Configuration 1 - 8ms wake up */
	.APPEND = 0x00,  /* Application Code Section End */
	.BOOTEND = 0x00,  /* Boot Section End */
};


/*****************************************************************************/
/*                          Global Variables                                 */
/*****************************************************************************/
volatile uint8_t TimerTickFlag;					// flag generated by periodic interrupt
uint8_t OneShot1Counter = 0;
uint8_t OneShot2Counter = 0;
uint8_t OneShot1State = 0;
uint8_t OneShot2State = 0;
uint8_t IncomingBuzz = 0;
uint8_t IncomingBuzzPrevious = 0;
uint8_t IncomingBuzzPreviousPrevious = 0;

uint8_t T20HzCounter = 0;						// used in the ISR


/*****************************************************************************/
int main(void)
{
	InitializeHardware();
	
    while (1)	// loop forever
    {
		if (TimerTickFlag == TRUE)
		{
			// Enable High-voltage controls:
			// Inputs: PushToRing (PB1) and 20Hz_clk (PB4)
			// Outputs: EnHVpositive (PB2) and EnHVnegative (PB3)
			if ((PORTB.IN & PIN1_bm) && (PORTB.IN & PIN4_bm))			// PushToRing true and 20Hz_clk is high
			{
				PORTB.OUTSET = PIN2_bm | PIN3_bm;	// RingGen goes positive
			}
			else if ((PORTB.IN & PIN1_bm) && ((~PORTB.IN) & PIN4_bm))	// PushToRing true and 20Hz_clk is low
			{
				PORTB.OUTCLR = PIN2_bm | PIN3_bm;	// RingGen goes negative
			}
			else																	// PushToRing false
			{
				PORTB.OUTCLR = PIN2_bm;				// HV+ set low (RingGen floating)
				PORTB.OUTSET = PIN3_bm;				// HV- set high (RingGen floating)
			}

			// One-shot routines:
			// Inputs: IncomingBuzz (PC3) and BuzzClk (PA5)
			// Outputs: OneShot25 (PA3) and Buzzer_Amp_Enable (PC1)
			// One-Shot 1 is set for 25 ms
			// One-Shot 2 is set for 150 ms
			if (PORTC.IN & PIN3_bm)			// IncomingBuzz pin
			{
				IncomingBuzz = TRUE;
			}
			else
			{
				IncomingBuzz = FALSE;
			}
			
			
			// One-shot 1 routine: (25 ms)
			if (IncomingBuzz && IncomingBuzzPrevious && (~IncomingBuzzPreviousPrevious))		// rising edge (debounced)
			{
				OneShot1Counter = 2;				// Timer Tick is 8.33 ms, one-shot set for 25 ms, hence counter = (25ms/8.33ms) - 1 = 2
				OneShot1State = TRUE;
				PORTA.OUTSET = PIN3_bm;
			}
			else
			{
				if (OneShot1Counter != 0) OneShot1Counter--;
			}
			
			if (OneShot1Counter == 0)
			{
				OneShot1State = FALSE;
				PORTA.OUTCLR = PIN3_bm;
			}
			
			// One-shot 2 routine (150 ms, re-triggerable):
			if (IncomingBuzz && IncomingBuzzPrevious)				// rising edge (debounced)
			{
				OneShot2Counter = 18;				// Timer Tick is 8.33 ms, one-shot set for 150 ms, hence counter = 150ms/8.33mm = 18
			}
			if (OneShot2Counter != 0)
			{
				OneShot2Counter--;
				OneShot2State = TRUE;
				PORTC.OUTSET = PIN1_bm;
			}
			else
			{
				OneShot2State = FALSE;
				PORTC.OUTCLR = PIN1_bm;
			}
			
			
			// End of loop cleanup code:
			TimerTickFlag = FALSE;									// done with the loop
			IncomingBuzzPrevious = IncomingBuzz;					// used for de-bounced rising edge detector
			IncomingBuzzPreviousPrevious = IncomingBuzzPrevious;	// used for de-bounced rising edge detector
		}
    } // end while(forever)
} // end main()

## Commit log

2026-03-07 Update README.md
    First commit - not ready for prime time yet.
2026-03-08 Building directories
    added Firmware subdirectory
2026-03-08 Added goals and requirement doc
2026-04-24 beta version
2026-04-24 Blackbird version beta
2026-06-06 Update BOM and iBOM
    Minor changes to component package sizes and values.
2026-06-19 Update README.md
    Minor change in wording around "Status"
